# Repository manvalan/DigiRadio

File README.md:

<div align="center">

# DigiRadio

### DAB+/FM Bluetooth Receiver with SigmaDSP Audio Processing

**Open-source digital radio — Si4684 tuner · ADAU1701 SigmaDSP · Bluetooth aptX Adaptive · ESP32-S3**

</div>

---

## Overview

**DigiRadio** is an open-source digital radio receiver that combines terrestrial
broadcast reception (**DAB+ / DAB / FM**) with a programmable audio-processing
stage and high-quality **Bluetooth** audio output.

Incoming broadcast audio is decoded by a Silicon Labs **Si4684** digital-radio
receiver, processed by an Analog Devices **ADAU1701 SigmaDSP** (equalisation,
mixing, level control), and transmitted over Bluetooth by a Qualcomm QCC3056-based
**Feasycom FSC-BT1035** module supporting the **aptX Adaptive** codec. An Espressif
**ESP32-S3** acts as the host controller, orchestrating the three subsystems and
providing Wi-Fi connectivity, encrypted credential storage, and a browser-based
configuration UI.

The entire tuner → DSP → Bluetooth path is **fully digital (I²S, 48 kHz / 24-bit)** —
no analogue conversions are introduced between the tuner and the wireless link.

```
 FM/DAB antenna → [ Si4684 ] --I²S--> [ ADAU1701 DSP ] --I²S--> [ FSC-BT1035 ] → aptX
                       ↑                     ↑                        ↑
                       └──── SPI ──── [ ESP32-S3 host ] ──── UART ────┘
                                             │  I²C
                                      Wi-Fi · NVS · HTTP UI
```

---

## Key Features

### Hardware

> **v2 board:** the second board, with an ADAU1452 DSP, is in [`Hardware-v2/`](Hardware-v2/) (KiCad project and its own [firmware](Hardware-v2/firmware/)). Everything below describes the first board.

- **DAB+ / DAB / FM** reception (Si4684) via external whip antenna (SMA)
- **Fully digital audio path** — no avoidable A/D–D/A conversions
- **Programmable audio processing** on the ADAU1701 SigmaDSP
- **Bluetooth 5.2** output with **aptX / aptX HD / aptX Adaptive**
- **ESP32-S3** host with native USB, Wi-Fi and BLE
- **USB-C powered**; single-rail 3.3 V + low-noise 1.8 V for the tuner
- **6-layer impedance-controlled PCB**, 50 × 90 mm, two ground planes
- Three antennas (ESP32 2.4 GHz, BT1035 2.4 GHz, FM/DAB SMA) with proper keep-outs

### Firmware (ESP-IDF, C++23 — fw **0.13.0**)

| Area | Capability |
|------|------------|
| **Boot & chips** | Si4684 DAB+FM firmware load (HOST_LOAD blobs), ADAU1701 RAM program at every boot, BT1035 I2S slave init (`AT+AUXCFG=3`, `AT+I2SCFG=67`) |
| **Tuner** | FM tune/seek, DAB ensemble tune, service scan & play, RSQ/RDS, DAB event status |
| **Now playing** | FM RDS (PS, RadioText, PI, PTY) and DAB Dynamic Label (DLS) in status JSON and web UI |
| **Audio** | 6-band EQ, input mixer, stereo/bass enhancement overlays, profile persist in encrypted NVS |
| **Presets** | Station list CRUD, reorder, recall with audio profile re-apply, last-preset restore at boot |
| **Bluetooth** | Discoverable pairing, A2DP status, disconnect |
| **Network** | SoftAP setup mode, STA provisioning, tabbed gzipped SPA (`/`), typed JSON REST API |
| **Security** | NVS + flash encryption at rest (dev mode); keys never in repo |
| **Quality** | **13** host unit tests, 4 CI jobs (tests, Doxygen, manual sync, blob policy) |

Architecture follows a **functional core + imperative shell**: pure domain logic
(compilation, JSON, EQ design, RDS/DLS parsing) runs on the host under `ctest`;
drivers and FreeRTOS live in thin ESP-IDF components. See [`Software/AGENTS.md`](Software/AGENTS.md).

---

## Firmware Progress

Releases on `main` (newest first; builds are published as [GitHub releases](https://github.com/manvalan/DigiRadio/releases)):

| Version | Highlights |
|---------|------------|
| **0.13.0** | SigmaDSP program v2, audio presets stored in the radio, click-free input changes, alarm crash fix |
| **0.12.x** | DAB DL+ and FM RT+ title/artist, complete FM RadioText, web radio heap headroom, hung OTA images roll back |
| **0.11.x** | Alarm table and sleep timer; Si4684 image store; first release builds from GitHub Actions |
| **0.10.x** | Working web radio, phone audio over TCP, OTA probation |
| **0.9.x** | RDS alternate frequencies and DAB service following, `/api/tuner/signal`, Bluetooth on/off, Wi-Fi reset |
| **0.8.5** | BT1035 I2S slave boot init (schematic-aligned); I2C pull-ups R1/R16 confirmed 2 kΩ; `Hardware/DATASHEET/` bundle |
| **0.8.4** | Dual OTA + DSP blob updates, EEPROM identity, System tab OTA/DSP upload |
| **0.8.3** | NVS + flash encryption (development mode), `initEncryptedStorage`, security docs |
| **0.8.2** | Tabbed Web UI (now-playing, 6-band EQ, all REST); Si4684 blob CI policy |
| **0.8.1** | `IntegrationService` — boot preset recall, tune orchestration (tuner + audio + NVS `last_preset`); services stub removed |
| **0.8.0** | Preset reorder API/UI; broadcast metadata (RDS + DAB DLS); `readDabServiceData` driver path |
| **0.7.1** | CI workflow (host tests, Doxygen, manual sync); Doxygen warnings cleared |
| **0.7.0** | Station presets (NVS `station_list`), BT1035 pairing, full `/api/stations/*` |
| **0.5–0.6** | ADAU1701 runtime EQ/mixer, Si4684 tuning & DAB service list, BT1035 driver |
| **0.3–0.4** | Secure store, Wi-Fi provisioning, companion-chip boot, walking skeleton |

**Next:** firmware for the [v2 board](Hardware-v2/); see ([`Software/docs/security-flash-nvs.md`](Software/docs/security-flash-nvs.md),
[`Software/docs/TODO.md`](Software/docs/TODO.md)). Contributing:
[`CONTRIBUTING.md`](CONTRIBUTING.md).

---

## Repository Structure

```
DigiRadio/
├── .github/workflows/        CI — host tests, Doxygen, manual sync, Si4684 blob policy
├── Hardware/
│   ├── schematics/           Schematic (PDF)
│   ├── gerber/               Gerber + drill (fabrication)
│   ├── bom/                  Bill of Materials
│   ├── pick-and-place/       CPL / centroid
│   ├── easyeda/              EasyEDA source
│   └── 3d/                   Renders / STEP
├── Hardware-v2/              Second board (ADAU1452) — see its README
│   ├── kicad/                KiCad project
│   └── firmware/             v2 firmware
├── Software/                 Firmware project root — open this in Cursor
│   ├── AGENTS.md             Authoritative coding rules for agents
│   ├── instructions.md       Agent kickoff & slice roadmap
│   ├── Doxyfile              API documentation gate
│   ├── components/
│   │   ├── core/             Pure domain (host-tested, no ESP-IDF)
│   │   ├── drivers/          Si4684, ADAU1701, BT1035
│   │   ├── services/         Tuner, audio, Bluetooth, station, integration
│   │   ├── secure_store/     NVS wrappers (Wi-Fi, profiles, presets)
│   │   └── net/              Wi-Fi, HTTP server, gzipped web UI
│   ├── docs/
│   │   ├── manual/           LaTeX technical manual (canonical)
│   │   ├── security-flash-nvs.md  NVS/flash encryption + HIL checklist
│   │   └── TODO.md           Agent backlog and completed tasks
│   ├── Firmware/             Si4684 blobs + ADAU1701 SigmaStudio export
│   ├── main/                 app_main, hardware bootstrap
│   └── tools/                fetch_si4684_firmware, check_*, gzip-www
├── CONTRIBUTING.md           human-facing dev guide
├── LICENSE                   CERN-OHL-S v2 (hardware)
└── README.md                 ← you are here
```

Build the manual from `Software/docs/manual/`:

```bash
cd Software/docs/manual && latexmk -lualatex manual.tex
```

---

## Getting Started

### Firmware (developers)

Open **`Software/`** as the Cursor project so `AGENTS.md` and `.cursor/rules/` load.

```bash
cd Software
idf.py set-target esp32s3
idf.py build
idf.py erase-flash flash   # once when first enabling encryption (0.8.3+)
idf.py -p <port> monitor
```

Host unit tests (no hardware):

```bash
cd Software
cmake -S components/core/test -B build-host \
      -DCMAKE_CXX_COMPILER="$(brew --prefix llvm)/bin/clang++"   # macOS
cmake --build build-host
ctest --test-dir build-host --output-on-failure
```

Quality gates (also enforced in CI):

```bash
cd Software
doxygen Doxyfile
python3 tools/check-manual-sync.py
python3 tools/check_si4684_blobs.py
```

Full build notes: [`Software/README.md`](Software/README.md) · security:
[`Software/docs/security-flash-nvs.md`](Software/docs/security-flash-nvs.md).

### First boot (device)

1. Power the board; ESP32 starts **SoftAP** setup mode (`DigiRadio-setup` — see manual).
2. Connect and open the gzipped web UI or call `GET /api/health`.
3. `POST /api/wifi` with STA credentials; device reboots into normal mode.
4. Tune via `/api/tuner/*`, manage presets via `/api/stations/*`, pair BT via `/api/bluetooth/*`.

Schemas, error tokens, and boot flow: [`Software/docs/manual/ch-api.tex`](Software/docs/manual/ch-api.tex).

---

## iOS App (igiRadio)

The companion iOS app **igiRadio** (tuning, presets, web radio, firmware
updates over Wi-Fi) is not part of this repository. It is currently
available as a beta on **TestFlight**: if you would like to try it,
contact the author (for example by opening an
[issue](https://github.com/manvalan/DigiRadio/issues)) to receive an invite.

---

## HTTP API (summary)

| Method | Path | Purpose |
|--------|------|---------|
| GET | `/api/health` | Status, firmware version, companion-chip flags |
| POST | `/api/wifi` | Provision STA credentials |
| GET | `/api/tuner/status` | Tuner snapshot incl. RDS/DLS metadata |
| GET | `/api/tuner/services` | DAB service list |
| POST | `/api/tuner/tune` · `/play` · `/seek` | Tuner control |
| GET/PUT | `/api/audio/profile` | ADAU1701 mixer + EQ |
| POST | `/api/audio/reset` · `/stereo-enhance` · `/bass-enhance` | Audio overlays |
| GET | `/api/bluetooth/status` | BT1035 state |
| POST | `/api/bluetooth/pair` · `/pair/stop` · `/disconnect` | Bluetooth control |
| GET/POST | `/api/stations` · `/remove` · `/reorder` · `/tune` | Preset list & recall |

Generated C++ API reference: run `doxygen Doxyfile` → `Software/docs/api/html/index.html`.

---

## Design Highlights

| Topic | Choice | Rationale |
|---|---|---|
| **Audio quality** | QCC3056 / aptX Adaptive | Codec dominates wireless quality; DAC lives in the sink |
| **Audio path** | Fully digital I²S | Avoids unnecessary A/D–D/A between tuner and Bluetooth |
| **I²S master** | ADAU1701 (12.288 MHz) | Clean ×256 → 48 kHz; avoids sample-rate mismatch |
| **Firmware style** | C++23, `std::expected`, RAII | Typed errors, host-testable core, no primitive obsession |
| **Stack-up** | 6-layer, 2× GND | Solid ground under RF, crystals and USB |
| **USB routing** | TOP, ref. GND | 90 Ω diff at manufacturable geometry |
| **Antennas** | 3 zones, diagonal 2.4 GHz | Coexistence separation + full-layer keep-outs |

---

## Status

| Layer | State |
|-------|--------|
| **Schematic** | Complete and reviewed |
| **PCB layout** | 6-layer, DRC clean, plane continuity verified |
| **BOM** | Finalised (manufacturable / sourced) |
| **Prototype** | Fabricated and assembled by PCBWay, working |
| **Firmware** | **0.13.0** on `main` — DAB+/FM, web radio, phone audio, alarms, OTA from the app |
| **Web UI** | Tabbed SPA covering every REST endpoint |
| **HIL** | Running on the assembled prototype |
| **Agent backlog** | Feature-complete on `main` (fw 0.13.0); see [`Software/docs/TODO.md`](Software/docs/TODO.md) |

---

## Manufacturing: fabrication and assembly by PCBWay

The DigiRadio board was fabricated and assembled by [PCBWay](https://www.pcbway.com/), who sponsored part of the cost ($100).

It's not an easy board to build by hand: 6 layers with impedance control, a QFN tuner (Si4684), an LQFP DSP, two 2.4 GHz modules and a USB-C connector. PCBWay handled fabrication and turnkey assembly, and the lead times were the normal technical ones for this kind of job. The only part they don't stock is the Feasycom FSC-BT1035, which I soldered by hand.

The part I want to highlight is the support. During bring-up I couldn't get the Si4684 tuner to work, and with a board like this it's hard to tell whether the problem is in the hardware or in the firmware. PCBWay's support team helped me check the board and the assembly, and that was essential: it let me rule out hardware problems and find the real cause. Without their help I would have spent much longer chasing the wrong issue.

The board is shared as a [project on PCBWay](https://www.pcbway.com/project/shareproject/DigiRadio_Open_Source_Hi_Fi_DAB_FM_Receiver_with_DSP_and_aptX_Adaptive_Blueto_a1952812.html), so you can order it directly. Disclosure: PCBWay gives me a small percentage of those orders as store credit.

**Technical notes.** The FSC-BT1035 footprint uses a BT806-compatible, pin-identical land pattern. Component
datasheets for design review live in
[`Hardware/DATASHEET/`](Hardware/DATASHEET/) (Si4684-A10, AN851, ADAU1701, FSC-BT1035).
See the [Technical Manual](Software/docs/manual/manual.tex) hardware chapter
and manufacturing notes for fabrication settings and MSL-3 handling of the BT
module.

---

## License

- **Hardware** (schematics, PCB, Gerbers, BOM): CERN-OHL-S v2 — see [`LICENSE`](LICENSE)
- **Firmware / Software**: Apache-2.0 — see [`Software/LICENSE`](Software/LICENSE)
- **Documentation**: CC BY 4.0

Intellectual property of the design remains with the author. You are free to study,
modify and build the hardware under the terms of the respective licenses.

---

## Author

**Michele Bigi** — Open-source hardware project.

*Contributions, issues and questions are welcome via the [issue tracker](https://github.com/manvalan/DigiRadio/issues).*

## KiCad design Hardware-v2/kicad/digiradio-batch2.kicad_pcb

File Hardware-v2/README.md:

# DigiRadio v2 (batch 2)

Hardware files for the second DigiRadio board. The first board lives in
[`../Hardware`](../Hardware).

The v2 board adds an ADAU1452 DSP. The KiCad project is in [`kicad/`](kicad/) and the
firmware for this board in [`firmware/`](firmware/).

Planned layout, matching `Hardware/`:

| Folder | Contents |
|---|---|
| `kicad/` | KiCad project (`.kicad_pro`, `.kicad_sch`, `.kicad_pcb`, `.kicad_dru`) |
| `firmware/` | Firmware for the v2 board |
| `schematics/` | Exported schematic PDF, netlist, 3D STEP |
| `gerber/` | Fabrication outputs |
| `bom/` | Bill of materials |
| `pick-and-place/` | Assembly positions |
| `3D/` | Renders |
| `DATASHEET/` | Datasheets for parts new to v2 |

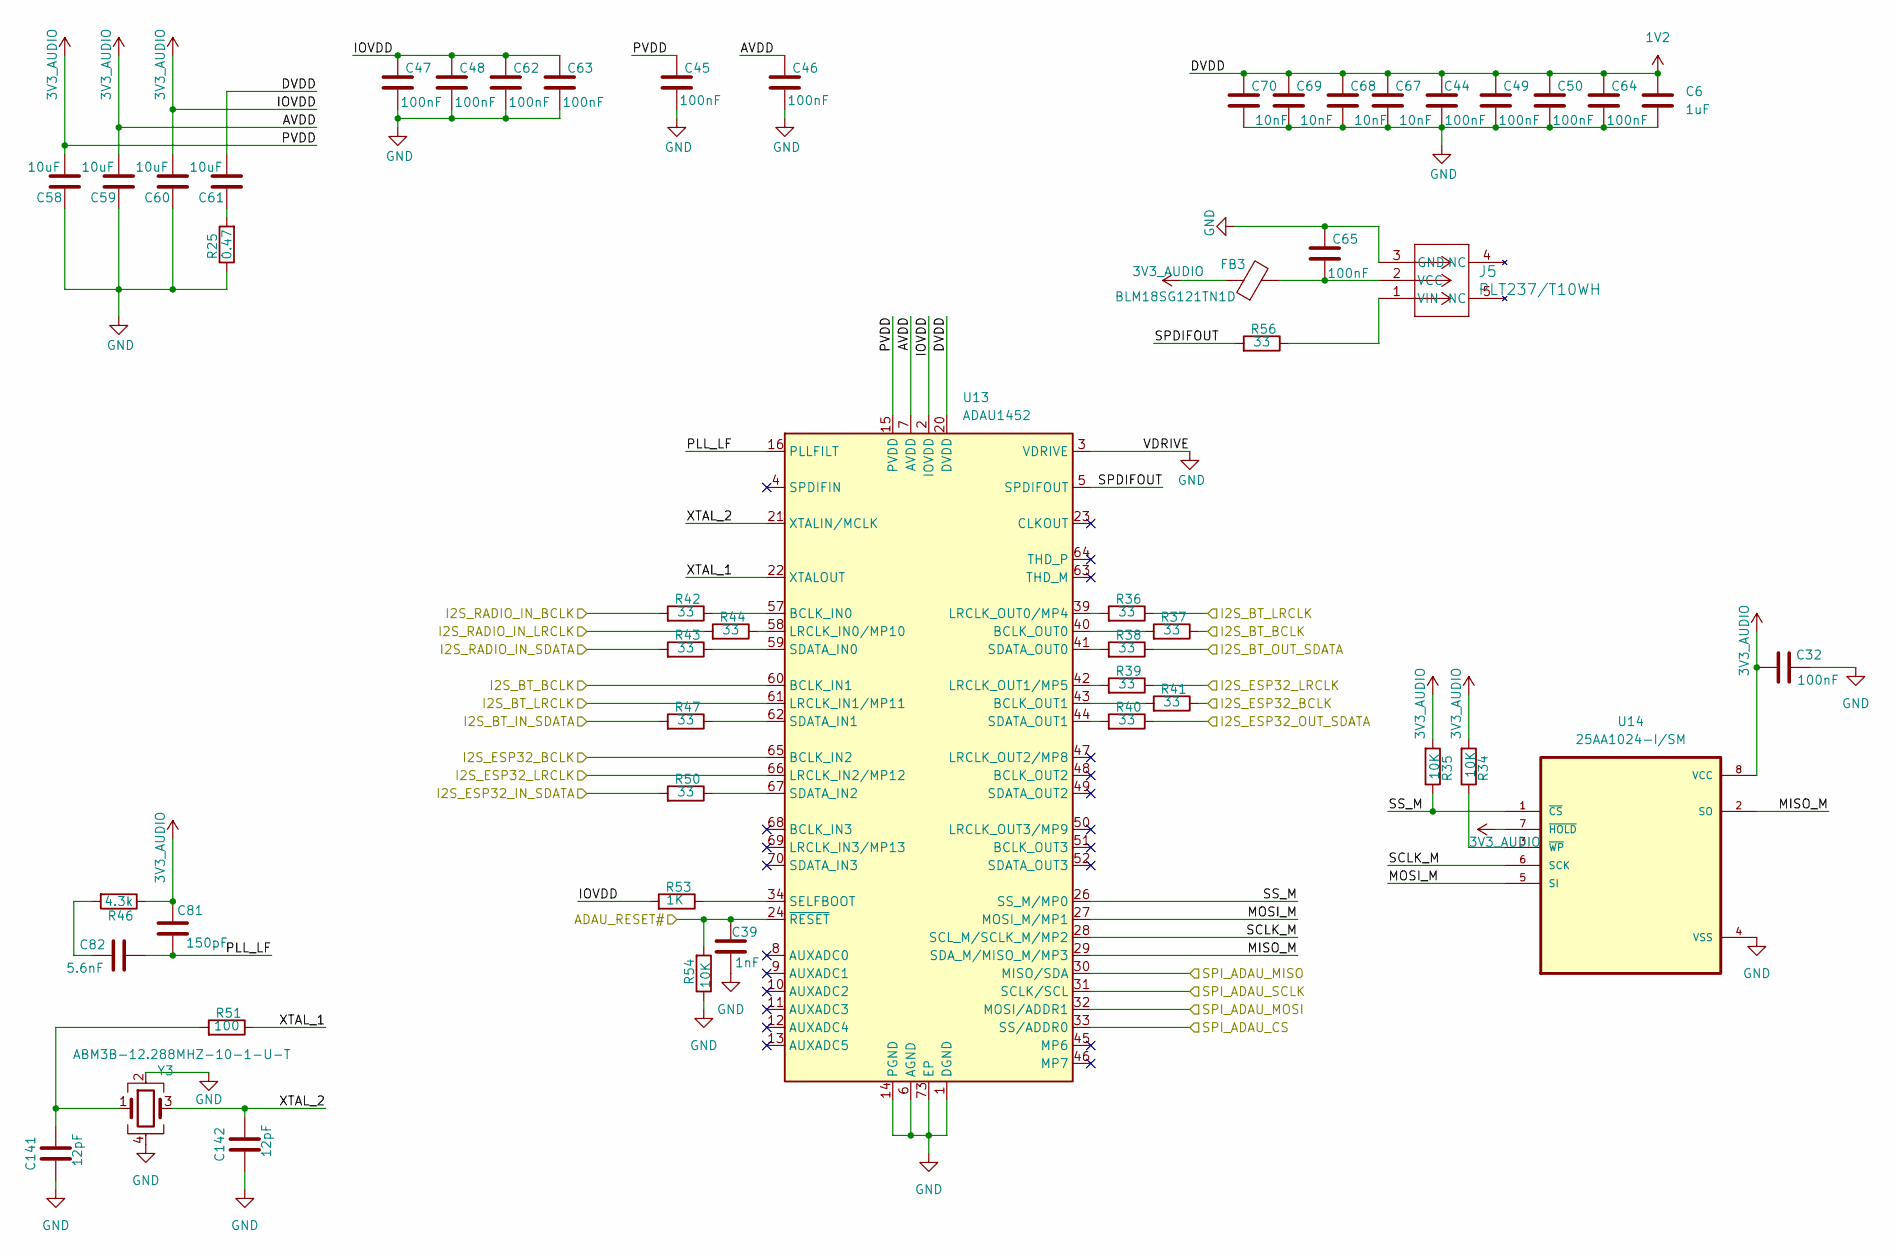
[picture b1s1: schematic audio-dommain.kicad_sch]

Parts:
C6: 1uF; C_0603_1608Metric
C32, C44, C45, C46, C47, C48, C49, C50, C62, C63, C64, C65: 100nF; C_0603_1608Metric
C39: 1nF; C_0603_1608Metric
C58, C59, C60, C61: 10uF; C_0805_2012Metric
C67, C68, C69, C70: 10nF; C_0603_1608Metric
C81: 150pF; C_0603_1608Metric
C82: 5.6nF; C_0603_1608Metric
C141, C142: 12pF; C_0603_1608Metric
FB3: BLM18SG121TN1D; L_0603_1608Metric; MPN BLM18SG121TN1D
J5: PLT237/T10WH; PLT237_T10WH
R25: 0.47; R_0603_1608Metric
R34, R35, R54: 10K; R_0603_1608Metric
R36, R37, R38, R39, R40, R41, R42, R43, R44, R47, R50, R56: 33; R_0603_1608Metric
R46: 4.3k; R_0603_1608Metric
R51: 100; R_0603_1608Metric
R53: 1K; R_0603_1608Metric
U13: ADAU1452; LFCSP-72-1EP_10x10mm_P0.5mm_EP5.3x5.3mm_ThermalVias
U14: 25AA1024-I/SM; SOIC-8_5.3x5.3mm_P1.27mm
Y3: ABM3B-12.288MHZ-10-1-U-T; Crystal_SMD_5032-4Pin_5.0x3.2mm

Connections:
1V2: C6.1, C44.1, C49.1, C50.1, C61.2, C64.1, C67.1, C68.1, C69.1, C70.1, U13.20 (DVDD), U13.35 (DVDD), U13.53 (DVDD), U13.71 (DVDD); also elsewhere on the board
3V3_AUDIO: C32.1, C45.1, C46.1, C47.1, C48.1, C58.2, C59.2, C60.2, C62.1, C63.1, C81.1, FB3.1, R34.2, R35.2, R46.1, R53.2, U13.2 (IOVDD), U13.7 (AVDD), U13.15 (PVDD), U13.18 (IOVDD), U13.38 (IOVDD), U13.56 (IOVDD), U14.7 (~HOLD), U14.8 (VCC); also elsewhere on the board
/AudioDomain/MISO_M: U13.29 (SDA_M/MISO_M/MP3), U14.2 (SO)
/AudioDomain/MOSI_M: U13.27 (MOSI_M/MP1), U14.5 (SI)
/AudioDomain/PLL_LF: C81.2, C82.2, U13.16 (PLLFILT)
/AudioDomain/SCLK_M: U13.28 (SCL_M/SCLK_M/MP2), U14.6 (SCK)
/AudioDomain/SPDIFOUT: R56.2, U13.5 (SPDIFOUT)
/AudioDomain/SS_M: R35.1, U13.26 (SS_M/MP0), U14.1 (~CS)
/AudioDomain/XTAL_1: R51.1, U13.22 (XTALOUT)
/AudioDomain/XTAL_2: C142.2, U13.21 (XTALIN/MCLK), Y3.3
ADAU_RESET#: C39.1, R54.2, U13.24 (~RESET); also elsewhere on the board
GND: C6.2, C32.2, C39.2, C44.2, C45.2, C46.2, C47.2, C48.2, C49.2, C50.2, C58.1, C59.1, C60.1, C62.2, C63.2, C64.2, C65.1, C67.2, C68.2, C69.2, C70.2, C141.1, C142.1, J5.3 (GND), R25.1, R54.1, U13.1 (DGND), U13.3 (VDRIVE), U13.6 (AGND), U13.14 (PGND), U13.17 (DGND), U13.19 (DGND), U13.25 (DGND), U13.36 (DGND), U13.37 (DGND), U13.54 (DGND), U13.55 (DGND), U13.72 (DGND), U13.73 (EP), U14.4 (VSS), Y3.2, Y3.4; also elsewhere on the board
I2S_BT_BCLK: R37.1, U13.60 (BCLK_IN1); also elsewhere on the board
I2S_BT_IN_SDATA: R47.2; also elsewhere on the board
I2S_BT_LRCLK: R36.1, U13.61 (LRCLK_IN1/MP11); also elsewhere on the board
I2S_BT_OUT_SDATA: R38.1; also elsewhere on the board
I2S_ESP32_BCLK: R41.1, U13.65 (BCLK_IN2); also elsewhere on the board
I2S_ESP32_IN_SDATA: R50.2; also elsewhere on the board
I2S_ESP32_LRCLK: R39.1, U13.66 (LRCLK_IN2/MP12); also elsewhere on the board
I2S_ESP32_OUT_SDATA: R40.1; also elsewhere on the board
I2S_RADIO_IN_BCLK: R42.2; also elsewhere on the board
I2S_RADIO_IN_LRCLK: R44.2; also elsewhere on the board
I2S_RADIO_IN_SDATA: R43.2; also elsewhere on the board
unnamed: C61.1, R25.2
unnamed: C82.1, R46.2
unnamed: C141.2, R51.2, Y3.1
unnamed: C65.2, FB3.2, J5.2 (VCC)
unnamed: J5.1 (VIN), R56.1
unnamed: R42.1, U13.57 (BCLK_IN0)
unnamed: R37.2, U13.40 (BCLK_OUT0)
unnamed: R41.2, U13.43 (BCLK_OUT1)
unnamed: R44.1, U13.58 (LRCLK_IN0/MP10)
unnamed: R36.2, U13.39 (LRCLK_OUT0/MP4)
unnamed: R39.2, U13.42 (LRCLK_OUT1/MP5)
unnamed: R43.1, U13.59 (SDATA_IN0)
unnamed: R47.1, U13.62 (SDATA_IN1)
unnamed: R50.1, U13.67 (SDATA_IN2)
unnamed: R38.2, U13.41 (SDATA_OUT0)
unnamed: R40.2, U13.44 (SDATA_OUT1)
unnamed: R53.1, U13.34 (SELFBOOT)
unnamed: R34.1, U14.3 (~WP)
SPI_ADAU_CS: U13.33 (SS/ADDR0); also elsewhere on the board
SPI_MISO: U13.30 (MISO/SDA); also elsewhere on the board
SPI_MOSI: U13.32 (MOSI/ADDR1); also elsewhere on the board
SPI_SCLK: U13.31 (SCLK/SCL); also elsewhere on the board

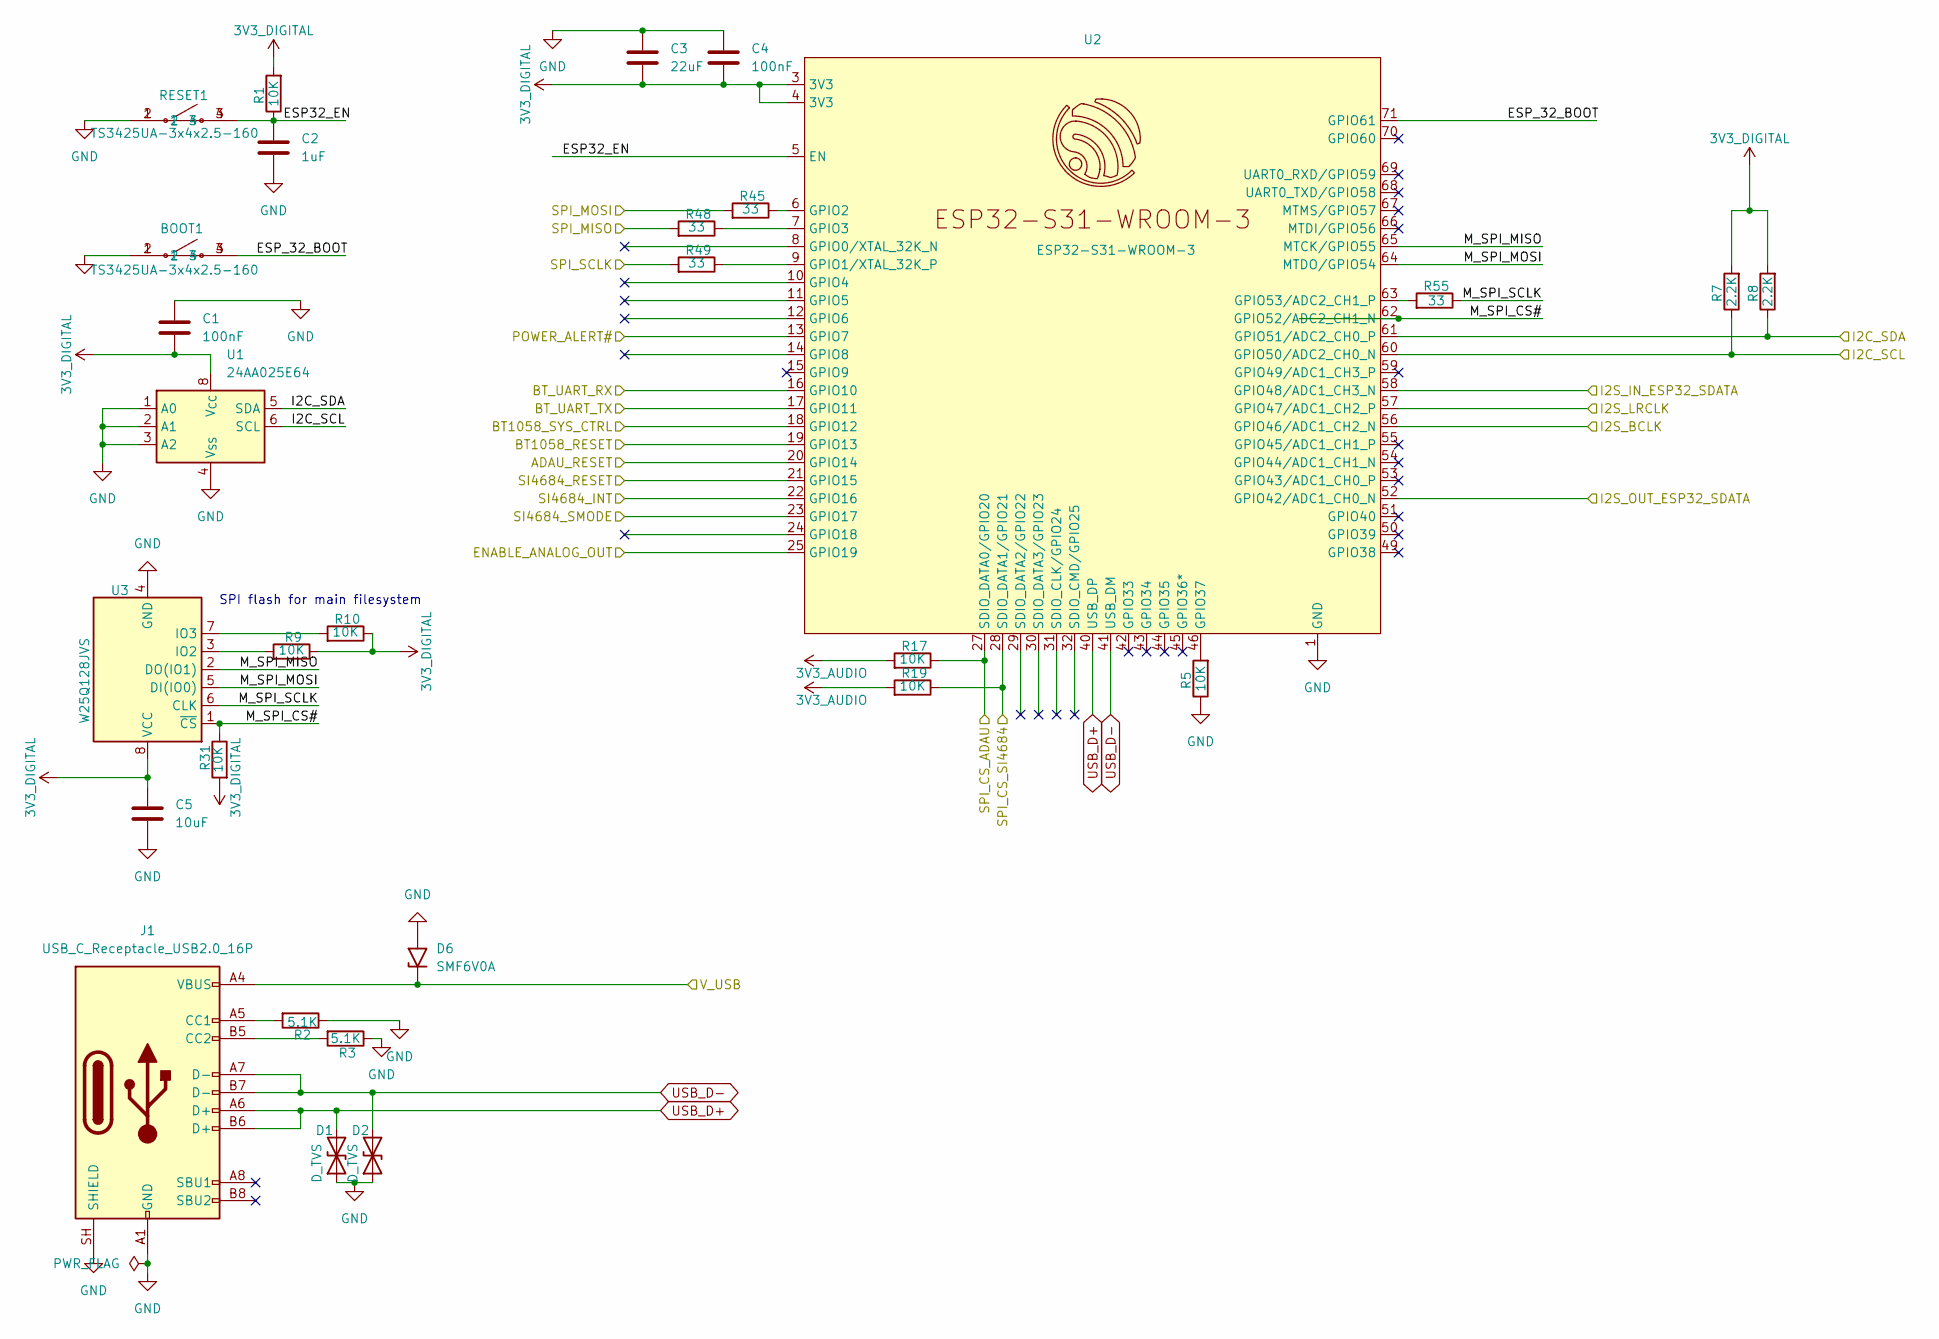
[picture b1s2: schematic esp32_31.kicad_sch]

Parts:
BOOT1: TS3425UA-3x4x2.5-160
C1, C4: 100nF; C_0603_1608Metric
C2: 1uF; C_0603_1608Metric
C3: 22uF; C_0805_2012Metric
C5: 10uF; C_1206_3216Metric
D1, D2: D_TVS; D_SOD-882
D6: SMF6V0A; D_SMF
J1: USB_C_Receptacle_USB2.0_16P; USB_C_Receptacle_HRO_TYPE-C-31-M-12
R1, R5, R9, R10, R17, R19, R31: 10K; R_0603_1608Metric
R2, R3: 5.1K; R_0603_1608Metric
R7, R8: 2.2K; R_0603_1608Metric
R45, R48, R49, R55: 33; R_0603_1608Metric
RESET1: TS3425UA-3x4x2.5-160
U1: 24AA025E64; SOIC-8_3.9x4.9mm_P1.27mm
U2: ESP32-S31-WROOM-3
U3: W25Q128JVS; SOIC-8_5.3x5.3mm_P1.27mm; LCSC Part # C97521

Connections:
3V3_AUDIO: R17.2, R19.2; also elsewhere on the board
3V3_DIGITAL: C1.2, C3.2, C4.2, C5.1, R1.2, R7.2, R8.2, R9.1, R10.1, R31.2, U1.8 (V_{CC}), U2.3 (3V3), U2.4 (3V3), U3.8 (VCC); also elsewhere on the board
/Esp32-S31/ESP32_EN: C2.1, R1.1, RESET1.3, RESET1.4, U2.5 (EN)
/Esp32-S31/ESP_32_BOOT: BOOT1.3, BOOT1.4, U2.71 (GPIO61)
/Esp32-S31/M_SPI_CS#: R31.1, U2.62 (GPIO52/ADC2_CH1_N), U3.1 (~CS)
/Esp32-S31/M_SPI_MISO: U2.65 (MTCK/GPIO55), U3.2 (DO(IO1))
/Esp32-S31/M_SPI_MOSI: U2.64 (MTDO/GPIO54), U3.5 (DI(IO0))
/Esp32-S31/M_SPI_SCLK: R55.1, U3.6 (CLK)
ADAU_RESET#: U2.20 (GPIO14); also elsewhere on the board
BT_RESET#: U2.19 (GPIO13); also elsewhere on the board
BT_SYS_CTRL: U2.18 (GPIO12); also elsewhere on the board
BT_UART_RX: U2.16 (GPIO10); also elsewhere on the board
BT_UART_TX: U2.17 (GPIO11); also elsewhere on the board
ENABLE_ANALOG: U2.25 (GPIO19); also elsewhere on the board
GND: BOOT1.1, BOOT1.2, C1.1, C2.2, C3.1, C4.1, C5.2, D1.1 (A1), D2.1 (A1), D6.2 (A2), J1.A1 (GND), J1.A12 (GND), J1.B1 (GND), J1.B12 (GND), J1.SH (SHIELD), R2.1, R3.1, R5.1, RESET1.1, RESET1.2, U1.1 (A0), U1.2 (A1), U1.3 (A2), U1.4 (V_{SS}), U2.1 (GND), U2.2 (GND), U2.26 (GND), U2.47 (GND), U2.48 (GND), U2.72 (GND), U2.73 (GND), U2.74 (GND), U2.75 (GND), U2.76 (GND), U2.77 (GND), U2.78 (GND), U2.79 (GND), U2.80 (GND), U2.81 (GND), U2.82 (GND), U2.83 (GND), U2.84 (GND), U2.85 (GND), U2.86 (GND), U2.87 (GND), U2.88 (GND), U2.89 (GND), U2.90 (GND), U2.92 (GND), U2.93 (GND), U2.94 (GND), U2.95 (GND), U2.96 (GND), U2.97 (GND), U2.98 (GND), U2.99 (GND), U3.4 (GND); also elsewhere on the board
I2C_SCL: R7.1, U1.6 (SCL), U2.60 (GPIO50/ADC2_CH0_N); also elsewhere on the board
I2C_SDA: R8.1, U1.5 (SDA), U2.61 (GPIO51/ADC2_CH0_P); also elsewhere on the board
I2S_ESP32_BCLK: U2.56 (GPIO46/ADC1_CH2_N); also elsewhere on the board
I2S_ESP32_IN_SDATA: U2.58 (GPIO48/ADC1_CH3_N); also elsewhere on the board
I2S_ESP32_LRCLK: U2.57 (GPIO47/ADC1_CH2_P); also elsewhere on the board
I2S_ESP32_OUT_SDATA: U2.52 (GPIO42/ADC1_CH0_N); also elsewhere on the board
unnamed: J1.A5 (CC1), R2.2
unnamed: J1.B5 (CC2), R3.2
unnamed: R49.1, U2.9 (GPIO1/XTAL_32K_P)
unnamed: R45.1, U2.6 (GPIO2)
unnamed: R48.1, U2.7 (GPIO3)
unnamed: R5.2, U2.46 (GPIO37)
unnamed: R55.2, U2.63 (GPIO53/ADC2_CH1_P)
unnamed: R9.2, U3.3 (IO2)
unnamed: R10.2, U3.7 (IO3)
PWR_ALERT: U2.13 (GPIO7); also elsewhere on the board
SI4684_INT: U2.22 (GPIO16); also elsewhere on the board
SI4684_RESET#: U2.21 (GPIO15); also elsewhere on the board
SI4684_SMODE: U2.23 (GPIO17); also elsewhere on the board
SPI_ADAU_CS: R17.1, U2.27 (SDIO_DATA0/GPIO20); also elsewhere on the board
SPI_MISO: R48.2; also elsewhere on the board
SPI_MOSI: R45.2; also elsewhere on the board
SPI_SCLK: R49.2; also elsewhere on the board
SPI_SI4684_CS: R19.1, U2.28 (SDIO_DATA1/GPIO21); also elsewhere on the board
USB_D+: D1.2 (A2), J1.A6 (D+), J1.B6 (D+), U2.40 (USB_DP)
USB_D-: D2.2 (A2), J1.A7 (D-), J1.B7 (D-), U2.41 (USB_DM)
V_USB: D6.1 (A1), J1.A4 (VBUS), J1.A9 (VBUS), J1.B4 (VBUS), J1.B9 (VBUS); also elsewhere on the board

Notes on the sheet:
SPI flash for main filesystem

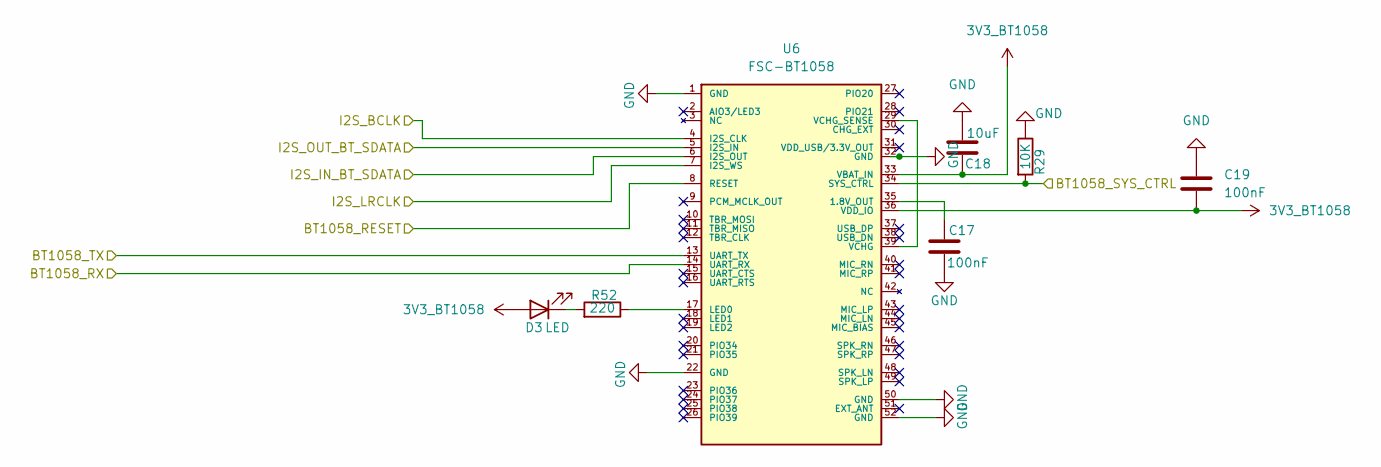
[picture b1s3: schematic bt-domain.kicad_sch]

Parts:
C17, C19: 100nF; C_0603_1608Metric
C18: 10uF; C_0805_2012Metric
D3: LED; LED_0805_2012Metric
R29: 10K; R_0603_1608Metric
R52: 220; R_0603_1608Metric
U6: FSC-BT1058

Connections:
3V3_BT1058: C18.1, C19.2, D3.2 (A), U6.33 (VBAT_IN), U6.36 (VDD_IO); also elsewhere on the board
BT_RESET#: U6.8 (RESET); also elsewhere on the board
BT_SYS_CTRL: R29.2, U6.34 (SYS_CTRL); also elsewhere on the board
BT_UART_RX: U6.13 (UART_TX); also elsewhere on the board
BT_UART_TX: U6.14 (UART_RX); also elsewhere on the board
GND: C17.2, C18.2, C19.1, R29.1, U6.1 (GND), U6.22 (GND), U6.32 (GND), U6.50 (GND), U6.52 (GND); also elsewhere on the board
I2S_BT_BCLK: U6.4 (I2S_CLK); also elsewhere on the board
I2S_BT_IN_SDATA: U6.6 (I2S_OUT); also elsewhere on the board
I2S_BT_LRCLK: U6.7 (I2S_WS); also elsewhere on the board
I2S_BT_OUT_SDATA: U6.5 (I2S_IN); also elsewhere on the board
unnamed: D3.1 (K), R52.2
unnamed: C17.1, U6.35 (1.8V_OUT)
unnamed: R52.1, U6.17 (LED0)
unnamed: U6.29 (VCHG_SENSE), U6.39 (VCHG)

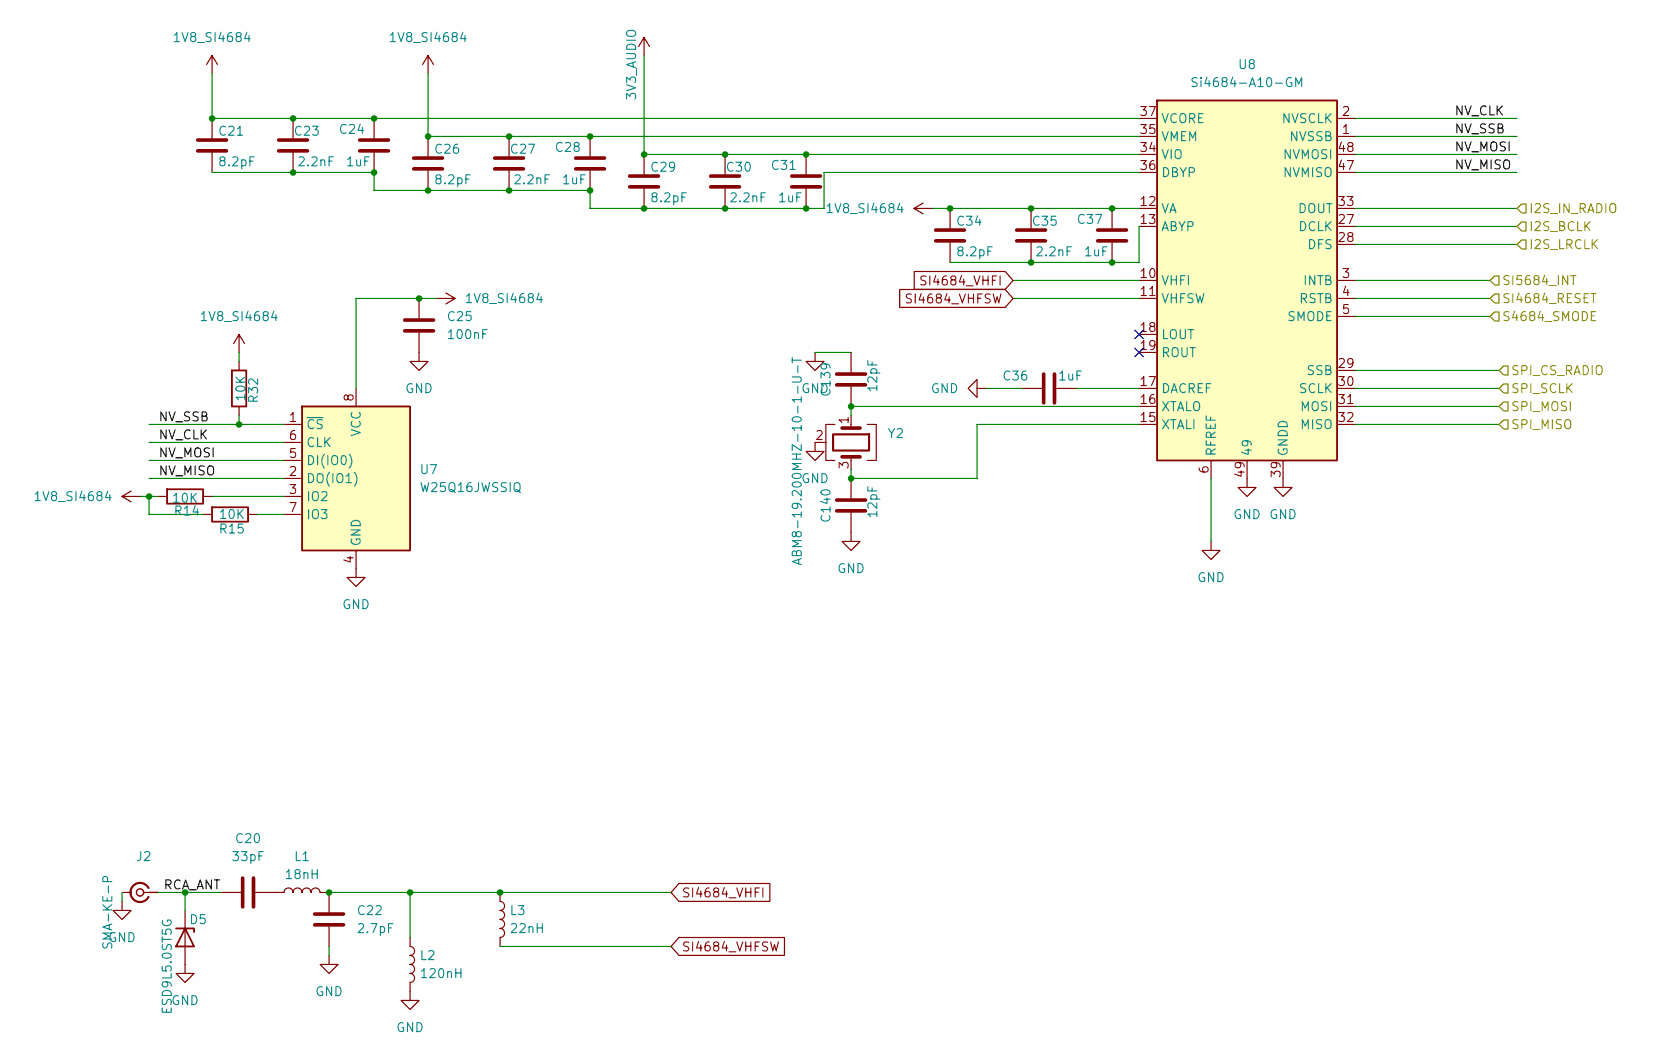
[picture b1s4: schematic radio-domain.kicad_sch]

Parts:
C20: 33pF; C_0603_1608Metric
C21, C26, C29, C34: 8.2pF; C_0603_1608Metric
C22: 2.7pF; C_0603_1608Metric
C23, C27, C30, C35: 2.2nF; C_0603_1608Metric
C24, C28, C31, C36, C37: 1uF; C_0603_1608Metric
C25: 100nF; C_0603_1608Metric
C139, C140: 12pF; C_0603_1608Metric
D5: ESD9L5.0ST5G; D_SOD-923
J2: SMA-KE-P; SMA-KE-P_EdgeMount
L1: 18nH; L_0603_1608Metric
L2: 120nH; L_0603_1608Metric
L3: 22nH; L_0603_1608Metric
R14, R15, R32: 10K; R_0603_1608Metric
U7: W25Q16JWSSIQ; SOIC-8_5.3x5.3mm_P1.27mm
U8: Si4684-A10-GM; QFN-48-1EP_7x7mm_P0.5mm_EP5.3x5.3mm_ThermalVias
Y2: ABM8-19.200MHZ-10-1-U-T; Crystal_SMD_Abracon_ABM8AIG-4Pin_3.2x2.5mm

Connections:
1V8_SI4684: C21.1, C23.1, C24.1, C25.1, C26.1, C27.1, C28.1, C34.1, C35.1, C37.1, R14.2, R15.2, R32.2, U7.8 (VCC), U8.12 (VA), U8.35 (VMEM), U8.37 (VCORE); also elsewhere on the board
3V3_AUDIO: C29.1, C30.1, C31.1, U8.34 (VIO); also elsewhere on the board
/Radio Domain/NV_CLK: U7.6 (CLK), U8.2 (NVSCLK)
/Radio Domain/NV_MISO: U7.2 (DO(IO1)), U8.47 (NVMISO)
/Radio Domain/NV_MOSI: U7.5 (DI(IO0)), U8.48 (NVMOSI)
/Radio Domain/NV_SSB: R32.1, U7.1 (~CS), U8.1 (NVSSB)
/Radio Domain/RCA_ANT: C20.1, D5.1 (K), J2.1 (In)
GND: C22.1, C25.2, C36.1, C139.2, C140.1, D5.2 (A), J2.2 (Ext), L2.2, U7.4 (GND), U8.6 (RFREF), U8.7 (RFREF), U8.8 (RFREF), U8.9 (RFREF), U8.39 (GNDD), U8.40 (GNDD), U8.41 (GNDD), U8.42 (GNDD), U8.49, Y2.2 (G), Y2.4 (G); also elsewhere on the board
I2S_RADIO_IN_BCLK: U8.27 (DCLK); also elsewhere on the board
I2S_RADIO_IN_LRCLK: U8.28 (DFS); also elsewhere on the board
I2S_RADIO_IN_SDATA: U8.33 (DOUT); also elsewhere on the board
unnamed: C20.2, L1.1
unnamed: R14.1, U7.3 (IO2)
unnamed: R15.1, U7.7 (IO3)
unnamed: C34.2, C35.2, C37.2, U8.13 (ABYP)
unnamed: C36.2, U8.17 (DACREF)
unnamed: C21.2, C23.2, C24.2, C26.2, C27.2, C28.2, C29.2, C30.2, C31.2, U8.36 (DBYP)
unnamed: C140.2, U8.15 (XTALI), Y2.3
unnamed: C139.1, U8.16 (XTALO), Y2.1
SI4684_INT: U8.3 (INTB); also elsewhere on the board
SI4684_RESET#: U8.4 (RSTB); also elsewhere on the board
SI4684_SMODE: U8.5 (SMODE); also elsewhere on the board
SI4684_VHFI: C22.2, L1.2, L2.1, L3.1, U8.10 (VHFI)
SI4684_VHFSW: L3.2, U8.11 (VHFSW)
SPI_MISO: U8.32 (MISO); also elsewhere on the board
SPI_MOSI: U8.31 (MOSI); also elsewhere on the board
SPI_SCLK: U8.30 (SCLK); also elsewhere on the board
SPI_SI4684_CS: U8.29 (SSB); also elsewhere on the board

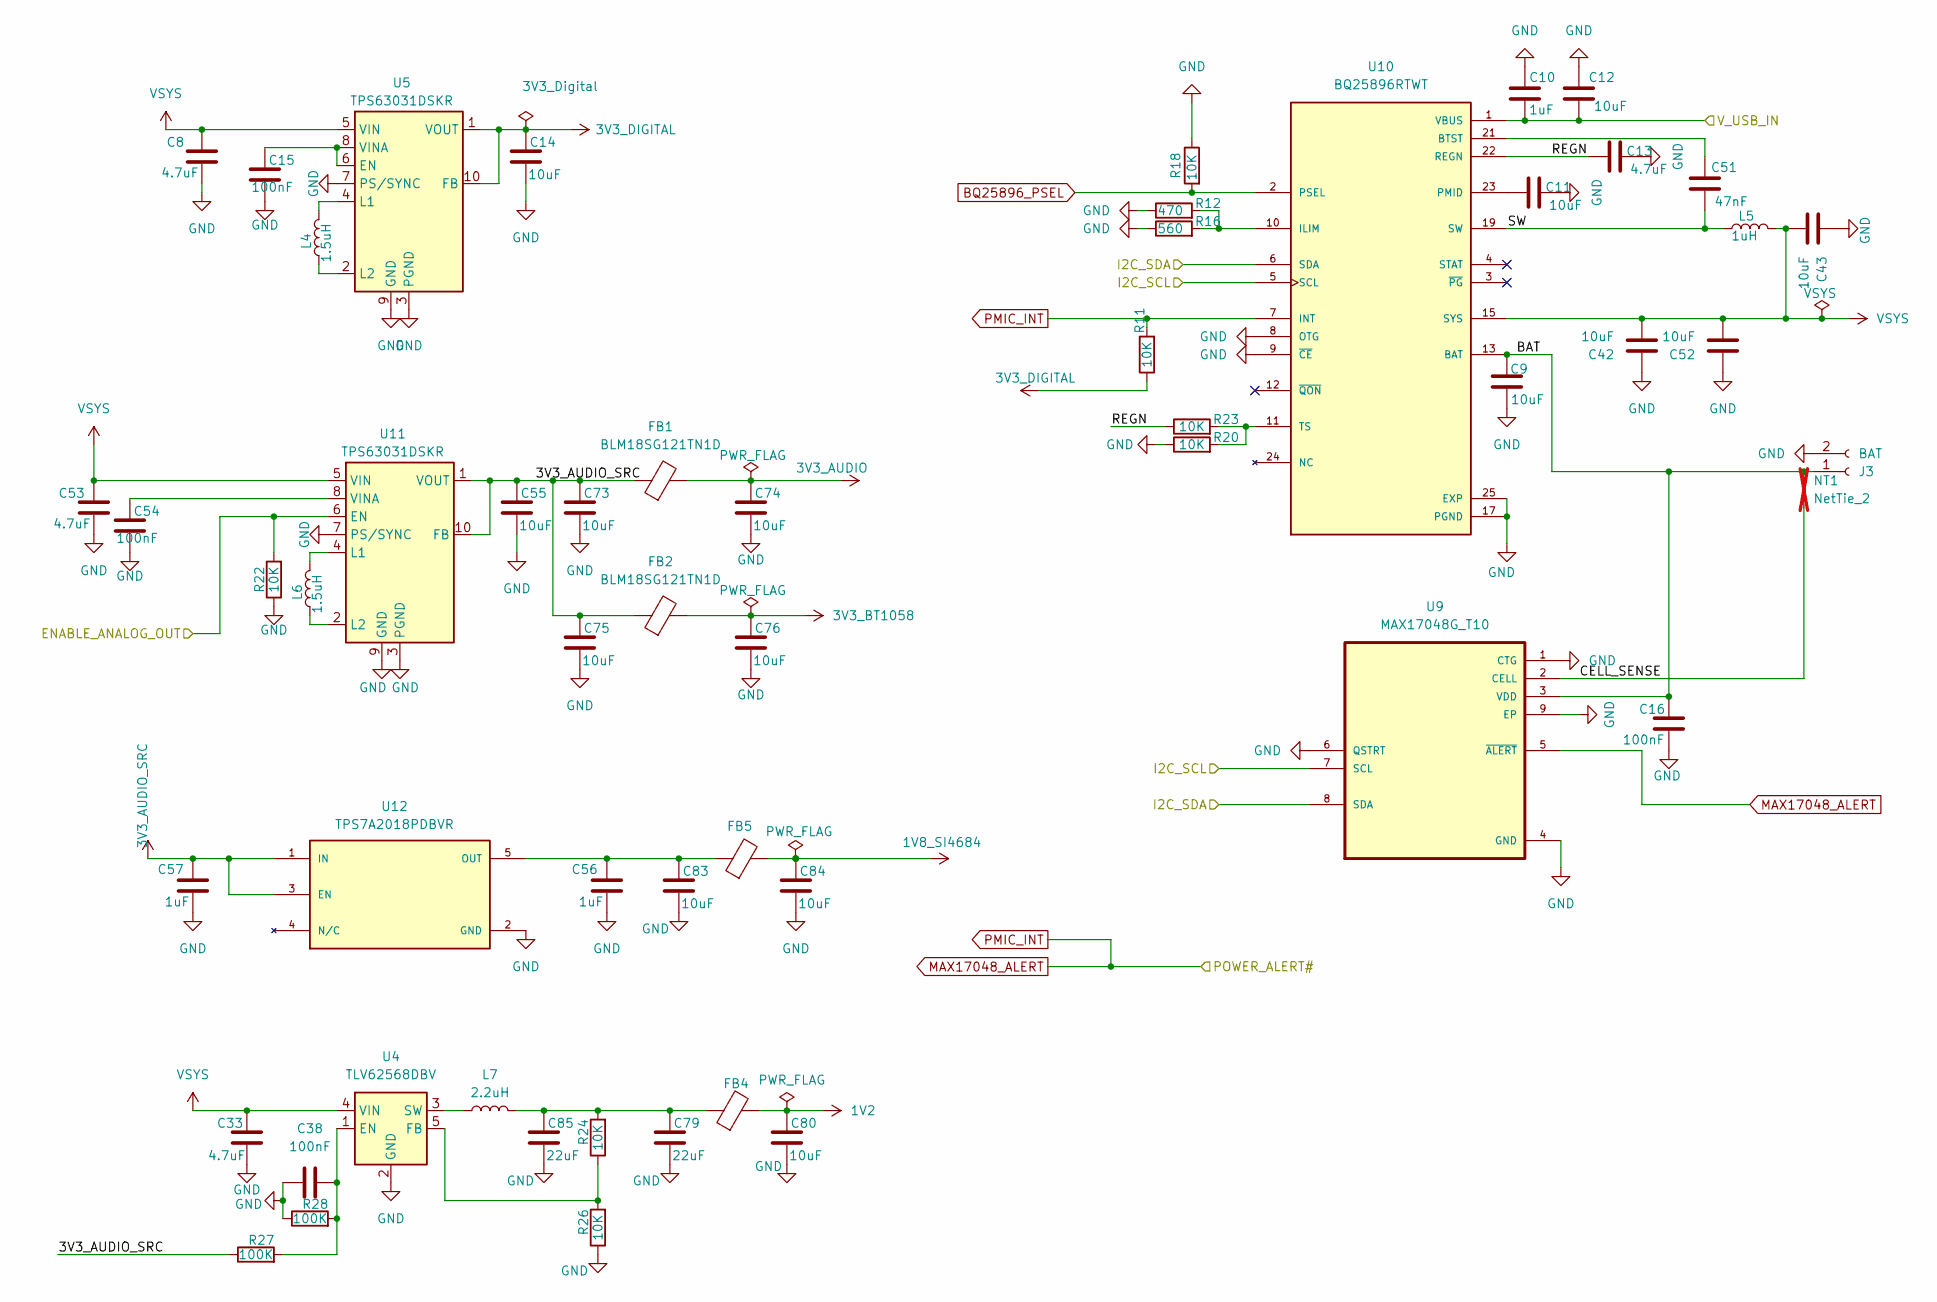
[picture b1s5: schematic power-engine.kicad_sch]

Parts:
C8, C13, C33, C53: 4.7uF; C_1206_3216Metric
C9, C11, C12, C14, C42, C52, C55, C73, C74, C75, C76, C80, C83, C84: 10uF; C_1206_3216Metric
C10, C56, C57: 1uF; C_0603_1608Metric
C15, C16, C38, C54: 100nF; C_0603_1608Metric
C43: 10uF; C_0603_1608Metric
C51: 47nF; C_0805_2012Metric
C79, C85: 22uF; C_1206_3216Metric
FB1, FB2, FB4, FB5: BLM18SG121TN1D; L_0603_1608Metric; MPN BLM18SG121TN1D
J3: BAT; JST_PH_S2B-PH-K_1x02_P2.00mm_Horizontal
L4, L6: 1.5uH; L_0805_2012Metric
L5: 1uH; L_Cenker_CKCS3015
L7: 2.2uH; L_APV_ANR4018
NT1: NetTie_2; NetTie-2_SMD_Pad0.5mm; not fitted
R11, R18, R20, R22, R23, R24, R26: 10K; R_0603_1608Metric
R12: 470; R_0603_1608Metric
R16: 560; R_0603_1608Metric
R27, R28: 100K; R_0603_1608Metric
U4: TLV62568DBV; SOT-23-5
U5, U11: TPS63031DSKR; WSON-10-1EP_2.5x2.5mm_P0.5mm_EP1.2x2mm_ThermalVias
U9: MAX17048G_T10; MAX17048G_T10_SON50P200X200X80-9N
U10: BQ25896RTWT; IC_BQ25896RTWT; PARTREV C
U12: TPS7A2018PDBVR; SOT95P280X145-5N; PARTREV H

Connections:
1V2: C80.2, FB4.2; also elsewhere on the board
1V8_SI4684: C84.2, FB5.2; also elsewhere on the board
3V3_AUDIO: C74.2, FB1.2; also elsewhere on the board
3V3_AUDIO_SRC: C55.2, C57.1, C73.2, C75.2, FB1.1, FB2.1, R27.1, U11.1 (VOUT), U11.10 (FB), U12.1 (IN), U12.3 (EN)
3V3_BT1058: C76.2, FB2.2; also elsewhere on the board
3V3_DIGITAL: C14.2, R11.1, U5.1 (VOUT), U5.10 (FB); also elsewhere on the board
/Power Engine/BAT: C9.2, C16.2, J3.1, NT1.2, U9.3 (VDD), U10.13 (BAT), U10.14 (BAT)
/Power Engine/CELL_SENSE: NT1.1, U9.2 (CELL)
/Power Engine/REGN: C13.2, R23.1, U10.22 (REGN)
/Power Engine/SW: C51.2, L5.1, U10.19 (SW), U10.20 (SW)
BQ25896_PSEL: R18.2, U10.2 (PSEL)
ENABLE_ANALOG: R22.2, U11.6 (EN); also elsewhere on the board
GND: C8.2, C9.1, C10.1, C11.1, C12.1, C13.1, C14.1, C15.1, C16.1, C33.2, C38.1, C42.1, C43.1, C52.1, C53.2, C54.1, C55.1, C56.2, C57.2, C73.1, C74.1, C75.1, C76.1, C79.1, C80.1, C83.1, C84.1, C85.1, J3.2, R12.1, R16.1, R18.1, R20.1, R22.1, R26.1, R28.1, U4.2 (GND), U5.3 (PGND), U5.7 (PS/SYNC), U5.9 (GND), U5.11 (PGND), U9.1 (CTG), U9.4 (GND), U9.6 (QSTRT), U9.9 (EP), U10.8 (OTG), U10.9 (~CE), U10.17 (PGND), U10.18 (PGND), U10.25 (EXP), U11.3 (PGND), U11.7 (PS/SYNC), U11.9 (GND), U11.11 (PGND), U12.2 (GND); also elsewhere on the board
I2C_SCL: U9.7 (SCL), U10.5 (SCL); also elsewhere on the board
I2C_SDA: U9.8 (SDA), U10.6 (SDA); also elsewhere on the board
unnamed: C79.2, C85.2, FB4.1, L7.2, R24.2
unnamed: C38.2, R27.2, R28.2, U4.1 (EN)
unnamed: R24.1, R26.2, U4.5 (FB)
unnamed: L7.1, U4.3 (SW)
unnamed: C15.2, U5.6 (EN), U5.8 (VINA)
unnamed: L4.2, U5.4 (L1)
unnamed: L4.1, U5.2 (L2)
unnamed: C51.1, U10.21 (BTST)
unnamed: R12.2, R16.2, U10.10 (ILIM)
unnamed: C11.2, U10.23 (PMID)
unnamed: R20.2, R23.2, U10.11 (TS)
unnamed: L6.2, U11.4 (L1)
unnamed: L6.1, U11.2 (L2)
unnamed: C54.2, U11.8 (VINA)
unnamed: C56.1, C83.2, FB5.1, U12.5 (OUT)
PWR_ALERT: R11.2, U9.5 (~ALERT), U10.7 (INT); also elsewhere on the board
VSYS: C8.1, C33.1, C42.2, C43.2, C52.2, C53.1, L5.2, U4.4 (VIN), U5.5 (VIN), U10.15 (SYS), U10.16 (SYS), U11.5 (VIN)
V_USB: C10.2, C12.2, U10.1 (VBUS); also elsewhere on the board

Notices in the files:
Hardware-v2/kicad/digiradio-batch2.kicad_pcb:
© Michele Bigi
README.md:
Hardware License
Firmware License: Apache 2.0
